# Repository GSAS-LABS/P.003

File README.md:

<h1 align="center">GSAS-LABS </br> P.003-V.1.0.1 </h1>

<p align="center">
  
</p>

<p align="center">
  Digital dice based on an ATtiny85 and 74HC595. Supports D4, D6, D8, and D10 modes, with configurable rolling animation, button-based type selection, EEPROM persistence, and low-power sleep mode for extended battery life.
</p>

# 🎲 Digital Dice

<p align="center">
  
  &nbsp;&nbsp;&nbsp;
  
  &nbsp;&nbsp;&nbsp;
  
</p>

P.003 is a compact digital dice designed around the ATtiny85 microcontroller.

The project uses a 74HC595 shift register to control the display while minimizing the number of microcontroller pins required.

The dice supports multiple modes and remembers the selected configuration between power cycles.

## Supported Dice

- 🎲 D4
- 🎲 D6
- 🎲 D8
- 🎲 D10

# 🎮 How to Use

## Power Switch

The board includes an ON/OFF power switch.

Move the switch to the **ON** position to power the device.

When the board is powered, the power indicator LED turns on, indicating that the circuit is active and ready to use.

Move the switch to the **OFF** position when the device is not being used. Turning the board off helps preserve battery life.

## Power Indicator

A dedicated LED indicates the power status of the board.

- **LED ON** — The board is powered and ready to use.
- **LED OFF** — The board is switched off.

For maximum battery life, turn the board off when it will not be used for an extended period.

## Buttons

The device includes two buttons:

- **ROLL / RESET**
- **MODE / SELECT**

Both buttons support short and long presses.

### ROLL / RESET

A **short press** rolls the currently selected dice.

The display performs the rolling animation and then shows the generated result.

A **long press** clears the display.

### MODE / SELECT

A **short press** changes the currently selected dice type.

The available dice types are:

```text
D4 → D6 → D8 → D10
```

A **long press** confirms the currently selected dice type.

While selecting a dice type, the led point (`.`) of the 7-segment display is illuminated to indicate that the device is in selection mode.

After confirming the selection with a long press, the decimal point turns off.

The confirmed dice type is remembered by the device and automatically restored the next time the board is powered on.

## Dice Modes

The device supports the following dice types:

| Mode | Possible Results |
|---|---|
| D4 | 1 to 4 |
| D6 | 1 to 6 |
| D8 | 1 to 8 |
| D10 | 0 to 9 |

> In D10 mode, the generated values range from `0` to `9`.

# 🔋 Battery & Power Consumption

The board is powered by a **CR2450 lithium coin cell**.

Power consumption depends on the display state and whether the power indicator LED is installed.

## Power Consumption

| Operating State | Approx. Current |
|---|---:|
| All 7-segment display segments ON | ~7.5 mA |
| Standby / Sleep — power indicator LED installed | ~0.65 mA |
| Standby / Sleep — power indicator LED not installed | ~0.05 mA |

The firmware uses the ATtiny85 **Power-down sleep mode** when the device is not being used. The ADC and unused peripherals are disabled during low-power operation to minimize battery consumption.

The power indicator LED is connected directly to the power circuit and therefore consumes approximately **0.60 mA continuously** when the board is switched ON. This increases the standby consumption from approximately **0.05 mA to 0.65 mA**.

For maximum battery life, omitting the power indicator LED significantly reduces the standby current.

## Estimated Battery Life

Using a CR2450 with a nominal capacity of approximately **620 mAh**:

| Operating State | Current | Theoretical Battery Life |
|---|---:|---:|
| Standby — LED installed | ~0.65 mA | ~954 hours / ~40 days |
| Standby — LED not installed | ~0.05 mA | ~517 days / ~1.42 years |
| All display segments ON continuously | ~7.5 mA | ~83 hours / ~3.4 days |

> Battery life values are theoretical estimates based on the nominal 620 mAh battery capacity and measured current consumption. Actual battery life will be lower and depends on battery voltage, discharge characteristics, temperature, pulse loads, and the device's operating cycle.

> The CR2450's rated capacity is specified under particular discharge conditions. Continuous operation at currents significantly above the manufacturer's standard drain can result in less usable capacity than the nominal 620 mAh rating.

# 🧾 PCB BOM

| Reference | Component | Value / Part | Quantity | Unit Price | Total |
|---|---|---|---:|---|---:|
| AFF1 | 7-Segment Display | Common Cathod  | 1 | R$ 2.50 | R$ 2.50 |
| BT1 | Battery Holder | BAT-HLD-006-SMT, 1x CR2450 | 1 | R$ 2.53 | R$ 2.53 |
| D1 | LED | 3 mm Through-Hole LED | 1 | R$ 0.15 | R$ 0.15 |
| Q1 | P-Channel MOSFET | BS250 | 1 | R$ 2.50 | R$ 2.50 |
| R1 | Resistor | 100 kΩ | 1 | R$ 0.05 | R$ 0.05 |
| R2 | Resistor | 2.2 kΩ | 1 | R$ 0.05 | R$ 0.05 |
| R3–R10 | Resistor | 1K Ω | 8 | R$ 0.05 | R$ 0.40 |
| SW1 | Slide Switch | Micro Chave SS12D07 | 1 | R$ 0.50  | R$ 0.50  |
| SW2-SW3 | Push Button | 6 mm Tactile Switch | 2 | R$ 0.15  | R$ 0.30  |
| U1 | Microcontroller | ATTINY85-20PU, DIP-8 | 1 | R$ 26.00 | R$ 26.00 |
| U2 | Shift Register | SN74HC595N, DIP-16 | 1 | R$ 2.52  | R$ 2.52 |

## 💰 Estimated Cost

| Item | Estimated Cost |
|---|---:|
| Electronic Components | R$ 37.50 |
| PCB Manufacturing | R$ 8.50 |
| **Estimated Total Project Cost** | **R$ 46** |

> Component prices may vary depending on supplier, quantity, shipping costs, and location.

> PCB manufacturing costs will be added once the board fabrication service and order quantity are defined.

# 📐 Schematic

The schematic is organized into the following functional blocks:

<p align="center">
  
  &nbsp;&nbsp;&nbsp;
  
</p>

<p align="center">
  
  &nbsp;&nbsp;&nbsp;
  
</p>

| Block | Description |
|---|---|
| 🔋 Power Supply | CR2450 coin cell, ON/OFF switch, and power indicator LED. |
| 🧠 ATtiny85 | Main microcontroller. |
| 🔁 74HC595 Shift Register | Drives the display segments using a minimal number of MCU pins. |
| 🔢 7-Segment Display | Shows the rolled result. |

# 📐 KiCad PCB Configuration

The PCB uses custom routing values configured specifically for this project.

## 📏 Board Dimensions

| Parameter | Dimension |
|---|---:|
| Width | 42 mm |
| Height | 78 mm |

## 🛤️ Track Widths

| Track Width | Recommended Use |
|---|---|
| 0.25 mm | Signal routing |
| 0.40 mm | Power and higher-current connections |

## 🔘 Via Configuration

| Parameter | Value |
|---|---:|
| Via Diameter | 0.8 mm |
| Drill Hole | 0.4 mm |

> These values are configured as custom routing presets in the KiCad project and should be maintained when modifying or extending the PCB design.

# 🛠 Development Environment

The firmware is developed and built using PlatformIO.

The project includes a Makefile that simplifies the most common development tasks.

## Requirements

- macOS
- Homebrew
- PlatformIO

# ⚙️ Makefile

The project provides the following commands.

## Install PlatformIO

```bash
make install
```

This command checks whether PlatformIO is already installed.

If PlatformIO is not available, it installs PlatformIO using Homebrew.

## Update PlatformIO

```bash
make update
```

Updates PlatformIO and prints the installed version.

## Build Firmware

```bash
make build
```

## Program ATtiny85 Fuses

```bash
make fuses
```

## Upload Firmware

```bash
make upload
```

# 🔌 Programming the ATtiny85

The ATtiny85 is programmed using the ISP protocol.

The required signals are:

| Signal | Function |
|---|---|
| MOSI | Master Out Slave In |
| MISO | Master In Slave Out |
| SCK | Serial Clock |
| RESET | Programming Reset |
| VCC | Target Power |
| GND | Ground |

The board can be programmed using an ISP programmer such as a USBasp.

## ISP Connection

```text
USBasp              ATtiny85 PCB

MOSI   ──────────── MOSI
MISO   ──────────── MISO
SCK    ──────────── SCK
RESET  ──────────── RESET
VCC    ──────────── VCC
GND    ──────────── GND
```

# 🐧 GSAS-LABS

GSAS-LABS is an independent engineering laboratory dedicated to the design, development, and exploration of electronics and software projects. It combines hardware and software engineering to create practical projects focused on embedded systems, microcontrollers, PCB design, and software development.

Areas of interest include:

- Embedded systems
- Microcontrollers
- PCB design
- Hardware prototyping
- Electronics
- Software engineering

# 📜 License

This project combines software and hardware, with each part released under its corresponding open-source license.

## 💻 Firmware

The firmware is licensed under the [GNU General Public License v3.0 (GPLv3)](https://www.gnu.org/licenses/gpl-3.0.html).

The firmware can be used, studied, modified, and redistributed. Any distributed modifications must remain open-source and be released under the GPLv3.

## 🔧 Hardware

The hardware design is licensed under the [CERN Open Hardware Licence v2 (CERN-OHL-S)](https://ohwr.org/licences/).

This includes the hardware design files, such as:

- Schematics
- PCB layouts
- KiCad project files
- Manufacturing files

The hardware design can be used, studied, modified, manufactured, and distributed. Hardware designs based on this project must preserve the same open and strongly reciprocal principles when distributed.

## 🐧 GSAS-LABS Name and Logo

The **GSAS-LABS name, logo, and visual identity are not covered by the software or hardware licenses**.

All rights to the GSAS-LABS name and logo are reserved by their respective owner.

Use of the GSAS-LABS name or logo does not imply endorsement, affiliation, or approval of derivative projects.

---

<p align="center">
  <strong>Experiment · Build · Learn · Share</strong>
</p>

<p align="center">
  Made with ❤️ by GSAS-LABS
</p>

<p align="center">
  
</p>

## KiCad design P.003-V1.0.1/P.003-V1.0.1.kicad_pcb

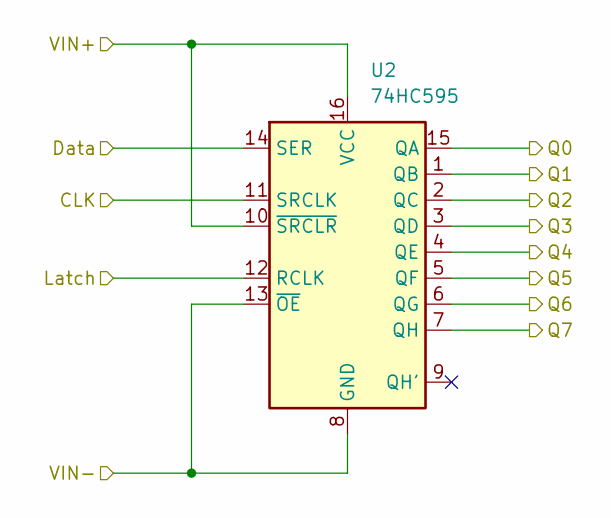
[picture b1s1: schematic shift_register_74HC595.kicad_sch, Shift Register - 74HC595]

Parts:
U2: 74HC595; DIP-16_W7.62mm

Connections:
/Attiny85/CLK: U2.11 (SRCLK); also elsewhere on the board
/Attiny85/Data: U2.14 (SER); also elsewhere on the board
/Attiny85/Latch: U2.12 (RCLK); also elsewhere on the board
/Attiny85/VIN+: U2.10 (~SRCLR), U2.16 (VCC); also elsewhere on the board
/Attiny85/VIN-: U2.8 (GND), U2.13 (~OE); also elsewhere on the board
/Display 7 Segment/Q0: U2.15 (QA); also elsewhere on the board
/Display 7 Segment/Q1: U2.1 (QB); also elsewhere on the board
/Display 7 Segment/Q2: U2.2 (QC); also elsewhere on the board
/Display 7 Segment/Q3: U2.3 (QD); also elsewhere on the board
/Display 7 Segment/Q4: U2.4 (QE); also elsewhere on the board
/Display 7 Segment/Q5: U2.5 (QF); also elsewhere on the board
/Display 7 Segment/Q6: U2.6 (QG); also elsewhere on the board
/Display 7 Segment/Q7: U2.7 (QH); also elsewhere on the board

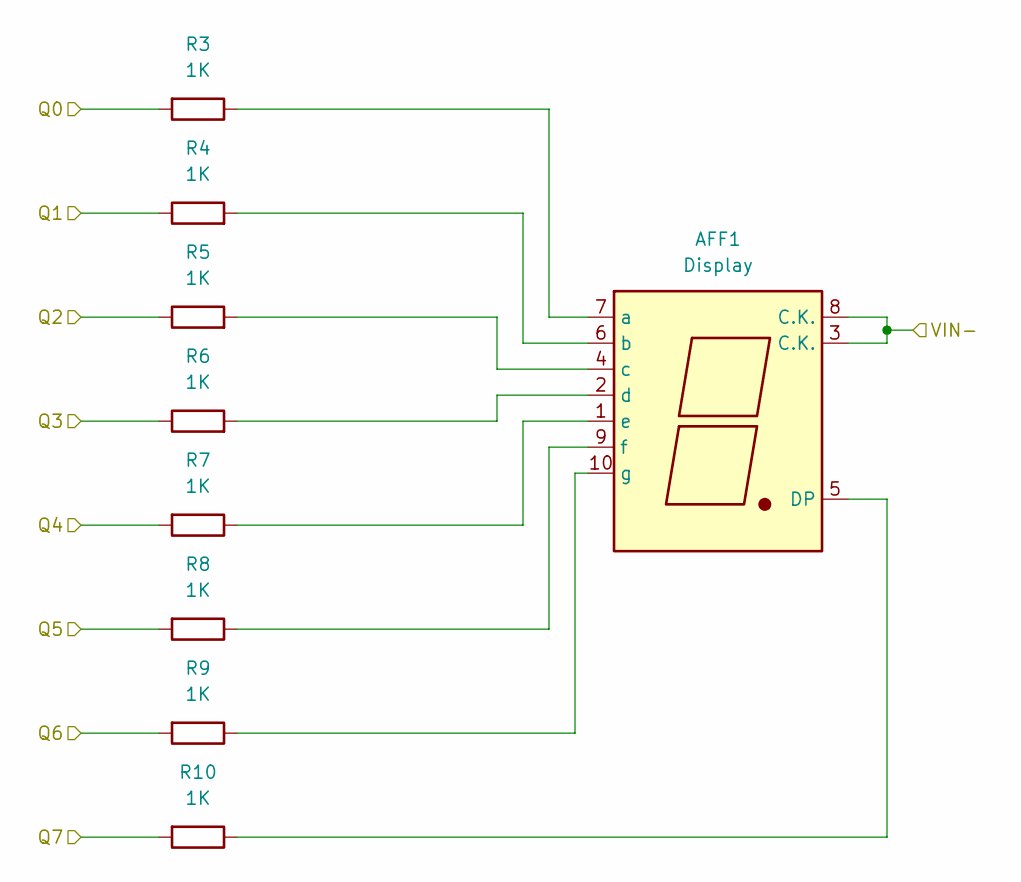
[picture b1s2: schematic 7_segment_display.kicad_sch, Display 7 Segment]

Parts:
AFF1: Display; 7SegmentLED_LTS6760_LTS6780
R3, R4, R5, R6, R7, R8, R9, R10: 1K; R_Axial_DIN0207_L6.3mm_D2.5mm_P10.16mm_Horizontal

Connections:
/Attiny85/VIN-: AFF1.3 (C.K.), AFF1.8 (C.K.); also elsewhere on the board
/Display 7 Segment/Q0: R3.2; also elsewhere on the board
/Display 7 Segment/Q1: R4.1; also elsewhere on the board
/Display 7 Segment/Q2: R5.1; also elsewhere on the board
/Display 7 Segment/Q3: R6.1; also elsewhere on the board
/Display 7 Segment/Q4: R7.2; also elsewhere on the board
/Display 7 Segment/Q5: R8.2; also elsewhere on the board
/Display 7 Segment/Q6: R9.2; also elsewhere on the board
/Display 7 Segment/Q7: R10.2; also elsewhere on the board
unnamed: AFF1.5 (DP), R10.1
unnamed: AFF1.7 (a), R3.1
unnamed: AFF1.6 (b), R4.2
unnamed: AFF1.4 (c), R5.2
unnamed: AFF1.2 (d), R6.2
unnamed: AFF1.1 (e), R7.1
unnamed: AFF1.9 (f), R8.1
unnamed: AFF1.10 (g), R9.1

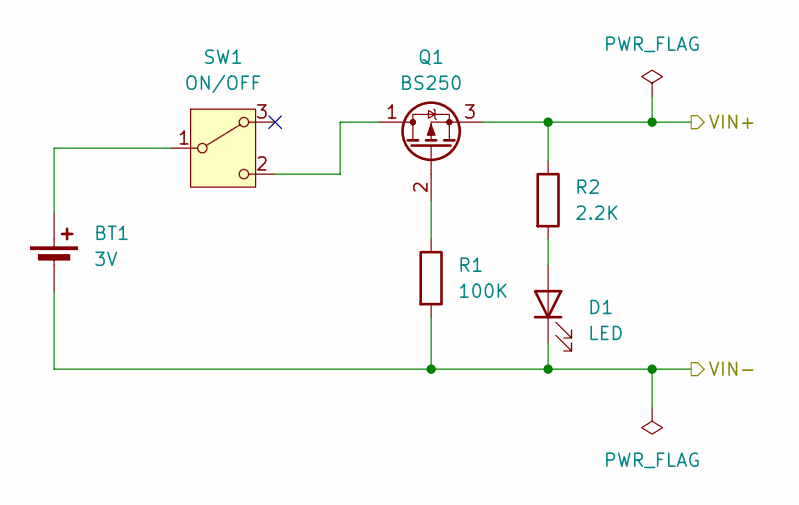
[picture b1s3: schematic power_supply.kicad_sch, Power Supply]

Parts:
BT1: 3V; BatteryHolder_Keystone_3008_1x2450
D1: LED; LED_D3.0mm
Q1: BS250; TO-92_Inline
R1: 100K; R_Axial_DIN0207_L6.3mm_D2.5mm_P10.16mm_Horizontal
R2: 2.2K; R_Axial_DIN0207_L6.3mm_D2.5mm_P10.16mm_Horizontal
SW1: ON/OFF; SW_Slide_SPDT_Straight_CK_OS102011MS2Q

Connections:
/Attiny85/VIN+: Q1.3 (S), R2.1; also elsewhere on the board
/Attiny85/VIN-: BT1.2 (-), D1.1 (K), R1.2; also elsewhere on the board
unnamed: BT1.1 (+), SW1.1 (B)
unnamed: D1.2 (A), R2.2
unnamed: Q1.1 (D), SW1.2 (C)
unnamed: Q1.2 (G), R1.1

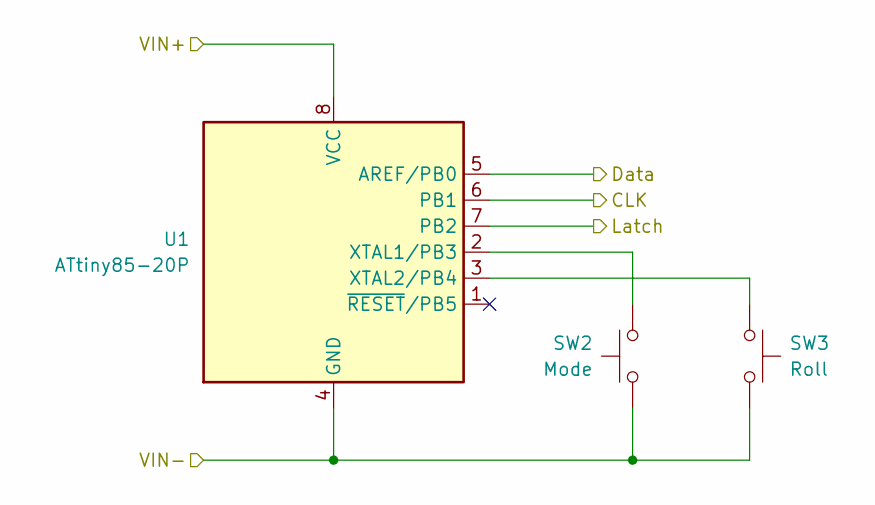
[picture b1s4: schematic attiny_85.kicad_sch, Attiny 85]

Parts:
SW2: Mode; SW_PUSH_6mm_H4.3mm
SW3: Roll; SW_PUSH_6mm_H4.3mm
U1: ATtiny85-20P; DIP-8_W7.62mm

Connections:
/Attiny85/CLK: U1.6 (PB1); also elsewhere on the board
/Attiny85/Data: U1.5 (AREF/PB0); also elsewhere on the board
/Attiny85/Latch: U1.7 (PB2); also elsewhere on the board
/Attiny85/VIN+: U1.8 (VCC); also elsewhere on the board
/Attiny85/VIN-: SW2.2, SW3.2, U1.4 (GND); also elsewhere on the board
unnamed: SW2.1, U1.2 (XTAL1/PB3)
unnamed: SW3.1, U1.3 (XTAL2/PB4)

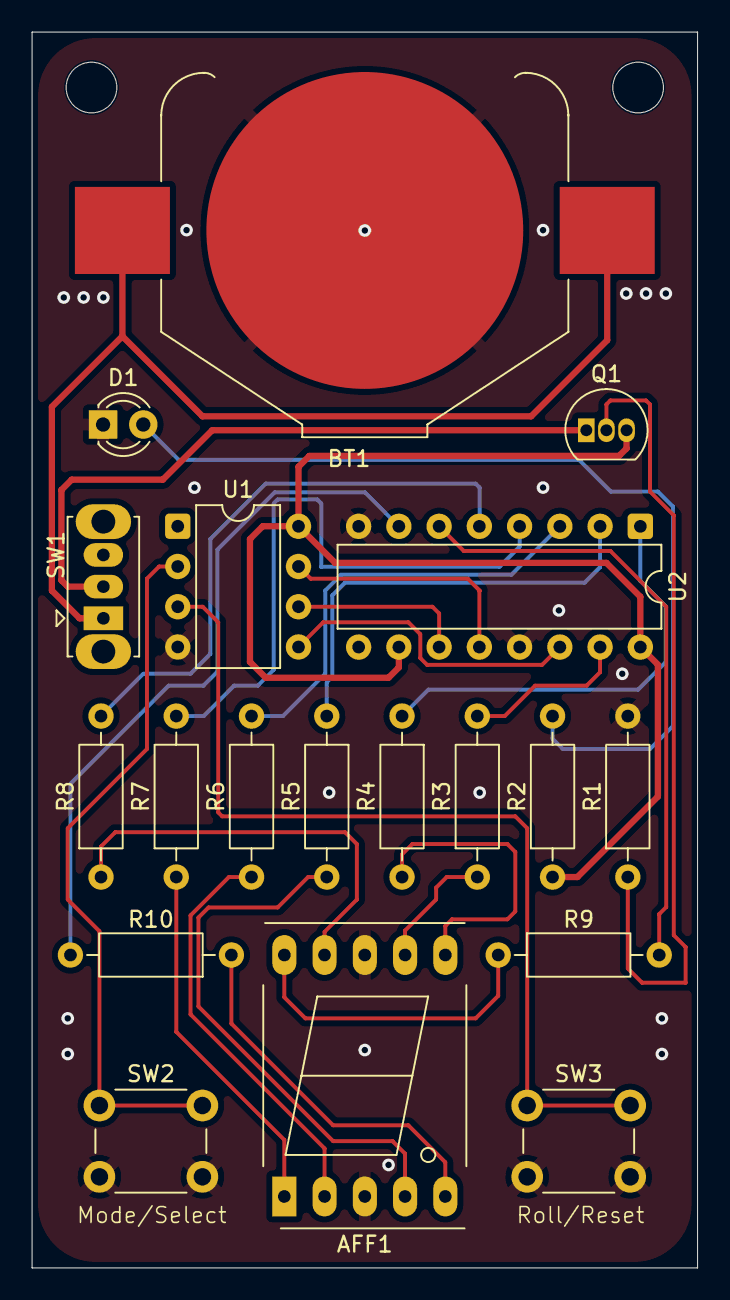
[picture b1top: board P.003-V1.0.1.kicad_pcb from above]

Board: 2 copper layers, 42.0 x 78.0 mm, 19 parts (0 on the bottom side), 27 nets.

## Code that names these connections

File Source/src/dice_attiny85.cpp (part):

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// ATtiny85 GPIO
// ============================================================

constexpr uint8_t PIN_DATA  = PB0;
constexpr uint8_t PIN_CLOCK = PB1;
constexpr uint8_t PIN_LATCH = PB2;

constexpr uint8_t PIN_BUTTON_TYPE = PB3;
constexpr uint8_t PIN_BUTTON_ROLL = PB4;

// ============================================================
// 74HC595
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void setup() {
    pinMode(PIN_DATA, OUTPUT);
    pinMode(PIN_CLOCK, OUTPUT);
    pinMode(PIN_LATCH, OUTPUT);

    pinMode(PIN_BUTTON_TYPE, INPUT_PULLUP);
    pinMode(PIN_BUTTON_ROLL, INPUT_PULLUP);

    digitalWrite(PIN_DATA, LOW);
    digitalWrite(PIN_CLOCK, LOW);
    digitalWrite(PIN_LATCH, HIGH);

    displayClear();
}
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// ============================================================

void shiftRegisterWrite(uint8_t value) {
    digitalWrite(PIN_LATCH, LOW);

    for (int8_t bit = 7; bit >= 0; bit--) {
        digitalWrite(PIN_CLOCK, LOW);
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    }

    digitalWrite(PIN_CLOCK, LOW);
    digitalWrite(PIN_LATCH, HIGH);
}


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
